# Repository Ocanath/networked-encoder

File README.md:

# Networked Encoder

A compact RS-485 magnetic encoder system powered by [DARTT](https://github.com/ocanath/dartt-protocol), designed for daisy-chaining multiple encoder nodes on a shared bus. The system consists of STM32-based firmware, a host-side C++ API, and a CLI tool for calibration, address assignment, and firmware flashing.

## What it does

Each encoder node sits on an RS-485 bus and responds to two address classes:

- **Motor address** — a minimal framing mode optimized for high-rate angle polling, intended for real-time motion control.
- **Misc address** — full DARTT register access for calibration (sin/cos bounds, angular offset, orthogonality error), device control (save to flash, restart, enter bootloader), and diagnostics.

Addresses are assigned per-device and persisted to flash. The bootloader (also DARTT-based) supports firmware updates over the same RS-485 bus with no additional hardware interface.

## Repository Structure

| Path | Contents |
|---|---|
| `embedded/encoder-rs485` | STM32G031 encoder application firmware |
| `embedded/encoder-bootloader` | DARTT-based RS-485 bootloader |
| `api/` | Host-side C++ encoder controller library |
| `cli/` | Command-line tool for calibration, addressing, and flashing |
| `scripts/` | Helper scripts for first-time device setup and firmware updates |

## Dependencies

The API and CLI pull in three submodules under `api/external/`:

| Submodule | Purpose |
|---|---|
| [`dartt-protocol`](https://github.com/ocanath/dartt-protocol) | DARTT framing, parsing, read/write helpers |
| [`byte-stuffing`](https://github.com/ocanath/byte-stuffing) | COBS encode/decode |
| [`serial-cross-platform`](https://github.com/ocanath/serial-cross-platform) | Cross-platform serial port |

Initialize all submodules after cloning with `git submodule update --init --recursive`.

## Building

Requires CMake 3.22+ and a C++20-capable compiler. The primary build target is `encoder-cli`. VSCode launch and build tasks are provided in `.vscode/`.

## CLI

The CLI (`encoder-cli`) takes a DARTT device address as its first argument followed by a port and baud rate. It supports streaming angle data, reading raw ADC values, running an interactive calibration session, reassigning device addresses, and flashing firmware over RS-485 via the bootloader. Run `encoder-cli --help` for the full command reference.

## First-time Device Setup

Use `scripts/init_flash.sh` to set up a brand-new device. The bootloader ships at address 255 and the encoder application defaults to address 0. The script flashes firmware, starts the application, then assigns a permanent address. For subsequent updates on an already-configured device, use `scripts/update_firmware.sh`.

## Using the API

`api/` is designed to be consumed as a CMake `add_subdirectory` dependency. Link against `encoder_controller` and construct an `Encoder` object with the device address and a pointer to an already-connected `Serial` object. The caller owns the `Serial` lifetime.

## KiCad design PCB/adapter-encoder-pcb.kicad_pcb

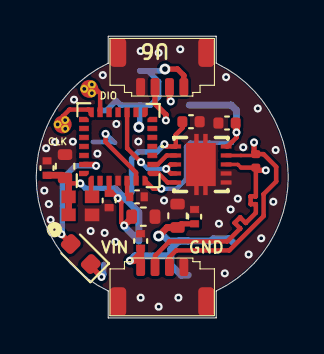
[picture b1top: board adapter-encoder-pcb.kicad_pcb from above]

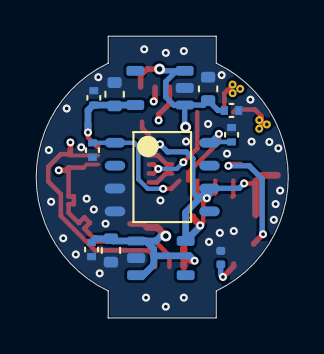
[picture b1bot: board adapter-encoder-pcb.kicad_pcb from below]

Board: 4 copper layers, 14.0 x 15.6 mm, 31 parts (12 on the bottom side), 17 nets.

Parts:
C1, C8, C10, C12, C15, C17: 4.7uF; C_0603_1608Metric
C2, C3, C4, C5, C6, C7, C9, C11, C13, C14, C16, C18: 100nF; C_0402_1005Metric
D1: LED; LED_0603_1608Metric
IC1: THVD2410VDRCR
M1, M2: THRU_HOLE_PAD; PAD-SMT-SMALL
R1: Resistor; R_0402_1005Metric
R3: 120; R_0402_1005Metric
U1: TLE5009E1000FUMA1; SOIC8-TLE5009
U2: STM32G031G6U6; UFQFPN28
U3, U6: DF52-4S-0.8H(21)
U4, U7: SPX3819M5-L-3-3; SOT-23-5
U5: C2901617; ECS-1633-480-BN-TR

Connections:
+3V3: C1.1, C3.1, C6.2, C12.1, C13.1, IC1.1 (VIO), U1.6 (Vdd), U2.3 (VDD), U4.5 (VOUT), U5.1 (Enable/Disable), U5.4 (VDD)
/+5V0: C7.2, C16.1, C17.1, IC1.10 (VCC), U7.5 (VOUT)
/COS: C2.1, U1.1 (COS_P), U2.7 (PA1)
/LED_GPIO: D1.2 (A), U2.27 (PB7)
/RS485+: IC1.8 (A), R3.1, U3.2, U6.2
/RS485-: IC1.9 (B), R3.2, U3.3, U6.3
/RX: IC1.2 (R), U2.9 (PA3)
/SIN: C4.1, U1.8 (SIN_P), U2.6 (PA0)
/SWCLK: M2.1, U2.20 (PA13)
/SWDIO: M1.1, U2.21 (PA14-BOOT0)
/TX: IC1.5 (D), U2.8 (PA2)
/UART1_DE: IC1.3 (DE), IC1.4 (~RE), U2.17 (PC6)
/Vin: C8.1, C9.1, C10.1, C11.1, C14.1, C15.1, C18.1, U3.1, U4.1 (VIN), U4.3 (EN), U6.1, U7.1 (VIN), U7.3 (EN)
GND: C1.2, C2.2, C3.2, C4.2, C5.2, C6.1, C7.1, C8.2, C9.2, C10.2, C11.2, C12.2, C13.2, C14.2, C15.2, C16.2, C17.2, C18.2, IC1.6 (GND), IC1.7 (SLR), IC1.11 (EP_1), IC1.12 (EP_2), IC1.13 (EP_3), IC1.14 (EP_4), IC1.15 (EP_5), R1.2, U1.3 (GND2), U1.4 (GND1), U2.4 (VSS), U3.4, U3.5 (MNT), U3.6 (MNT), U4.2 (GND), U5.2 (GND/Case), U6.4, U6.5 (MNT), U6.6 (MNT), U7.2 (GND)
unnamed: D1.1 (K), R1.1
unnamed: U2.1 (PC14-OSC32_IN), U5.3 (OUTPUT)
unnamed: C5.1, U2.5 (PF2-NRST)

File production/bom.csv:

Designator,Footprint,Quantity,Value,LCSC Part #
"C1, C10, C12, C15, C17, C8",0603,6,4.7uF,
"C11, C13, C14, C16, C18, C2, C3, C4, C5, C6, C7, C9",0402,12,100nF,
D1,0603,1,LED,
IC1,THVD2410VDRCR,1,THVD2410VDRCR,
R1,0402,1,Resistor,
"R2, R4",0402,2,1k,
R3,0402,1,120,
U1,SOIC8-TLE5009,1,TLE5009E1000FUMA1,
U2,UFQFPN28,1,STM32G031G6U6,
"U3, U6",DF52-4S-0.8H(21),2,DF52-4S-0.8H(21),
"U4, U7",SOT-23-5,2,SPX3819M5-L-3-3,
U5,ECS-1633-480-BN-TR,1,C2901617,ECS-1633-480-BN-TR

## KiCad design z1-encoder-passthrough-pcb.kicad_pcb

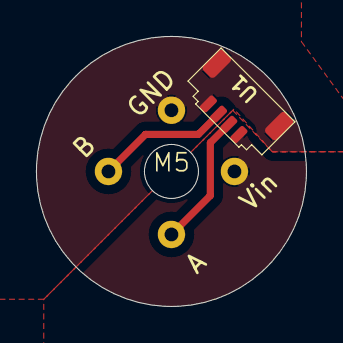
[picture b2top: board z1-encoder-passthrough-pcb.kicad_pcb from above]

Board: 2 copper layers, 15.0 x 15.0 mm, 6 parts (0 on the bottom side), 4 nets.

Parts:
M1, M2, M3, M4: THRU_HOLE_PAD; THRU_HOLE
M5: THRU_HOLE_PAD; MECH_THRU_HOLE
U1: DF52-4S-0.8H(21)

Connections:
/RS485+: M2.1, U1.2
/RS485-: M3.1, U1.3
/Vin: M1.1, U1.1
GND: M4.1, U1.4, U1.5 (MNT), U1.6 (MNT)

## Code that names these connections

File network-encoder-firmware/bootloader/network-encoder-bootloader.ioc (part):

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Mcu.Name=STM32G031G(4-6-8)Ux
Mcu.Package=UFQFPN28
Mcu.UserName=network-encoder-bootloader
PA0.GPIOParameters=GPIO_Label
PA0.GPIO_Label=SIN
PA0.Mode=IN0
PA0.Signal=ADC1_IN0
PA1.GPIOParameters=GPIO_Label
PA1.GPIO_Label=COS
PA1.Mode=IN1
PA1.Signal=ADC1_IN1
PA13.Mode=Serial_Wire
PA13.Signal=SYS_SWDIO
PA14-BOOT0.Mode=Serial_Wire
PA14-BOOT0.Signal=SYS_SWCLK
PA2.Mode=Asynchronous
PA2.Signal=USART2_TX
PA3.Mode=Asynchronous
PA3.Signal=USART2_RX
PB7.Signal=GPIO_Output
PC14-OSC32_IN\ (PC14).Mode=HSE-External-Clock-Source
PC14-OSC32_IN\ (PC14).Signal=RCC_OSC_IN
PC6.Signal=GPIO_Output
RCC.HSE_VALUE=48000000
RCC.SYSCLKFreq_VALUE=64000000
RCC.SYSCLKSource=RCC_SYSCLKSOURCE_PLLCLK
board=custom

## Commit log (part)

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2024-09-23 init commit
2024-10-03 new STM32, not enough RAM on the shitty L0. will probably need a little more OD but thats ok
2024-10-04 mostly routed updated board
2024-10-04 deleted unnecessary files, updated board outline, drc passes
2024-10-04 thickkness
2024-10-04 curves
2024-10-04 some minor tweaks
2024-10-12 length matching rs485
2024-10-13 cad and silkscreen
2024-10-14 designed the encoder CAD around the large 25mmID bearings
2024-10-14 patterned nuts
2024-10-14 updated screwhole style
2024-10-17 updated via size due to jlcpcb complaining about 0.4mm annular ring diameter
2024-11-17 ordered
2025-11-26 created a connector pcb for passthrough!
2025-11-26 stackup and step
2025-11-26 passthrough with pcb - pcb orderable and this is printable
2026-06-07 moved to pcb directory for this to be top level repo
2026-06-07 submodule added for networked encoder
2026-06-07 readme for visualizer added
2026-06-07 todo, gitignore, remove visualizer since that should be in a parent - this is a module
2026-06-12 update encoder efw
2026-06-12 add bootloader
2026-06-12 cleanup, gotta rename. shouldn't have named the project the target...
2026-06-12 rename bootloader
2026-06-12 ioc rename
2026-06-12 should have fixed build but no
2026-06-12 preprocessor, bootloader pinning dartt version
2026-06-12 update dartt
2026-06-14 bootloader
2026-06-14 vibed class
2026-06-14 submodules, namespace change
2026-06-14 action command added
2026-06-14 vibed cli tool
2026-06-14 cleared out all the vibed crap starting fresh
2026-06-14 wired up serial and read angle
2026-06-14 updated args parsing structure, addr positional now and optionals have --
2026-06-14 adc raw
2026-06-14 minimax
2026-06-14 calibration works
2026-06-14 write
2026-06-14 no launch
2026-06-14 bootloader address
2026-06-14 help
2026-06-14 pin update to bootloader which has public flasher api
2026-06-14 bootloader api updates
2026-06-14 trying motor msg implementation read angle
2026-06-14 firmware updated with read angle motor message
2026-06-14 q factor and sign extension
2026-06-14 misc command added
2026-06-14 helper scripts
2026-06-15 readme and version scripting
2026-06-15 dleete todo
2026-06-16 update top level readme
2026-06-16 byte stuffing readme
2026-06-16 updated dartt
2026-06-16 update serial readme
2026-06-16 bootloader readme
2026-06-16 readme updates
2026-06-16 rename embedded parent dir
2026-06-16 update gitmodules
2026-06-17 updated cad!
2026-06-20 regen with proper diameter.
2026-06-20 modified configurations and display states - created rendring assets
2026-06-20 created working urdf
2026-06-20 fixed collision primitives to cylinders for easier simulations
2026-06-20 print gitignore
2026-06-21 assets in meters now
2026-06-21 windows scripts, init flash works and update firmware should work too, so long as the tools are installed in the path
2026-06-21 solidworks regenerated everything, but added necessary x axis for constraining encoder assy
2026-06-21 no threads
